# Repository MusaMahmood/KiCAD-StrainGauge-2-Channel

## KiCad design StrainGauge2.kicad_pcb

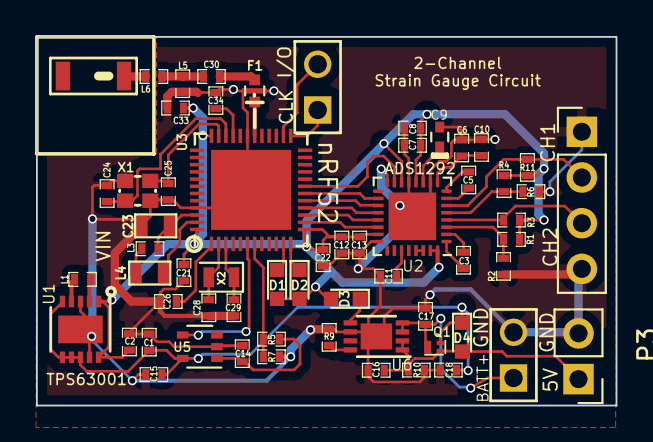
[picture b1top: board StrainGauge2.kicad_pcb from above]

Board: 2 copper layers, 32.2 x 20.5 mm, 61 parts (0 on the bottom side), 46 nets.

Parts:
A1: CHIP-ANT; JTI-2450AT18A100-CHIP-ANT
C1, C10, C14, C15: 10uF; SM0402
C2: 22uF; SM0402
C3, C5: 4.7 nF; SM0402
C6, C7, C12: 0.1uF; SM0402
C8, C11, C13: 1uF; SM0402
C9: 1uF; C_0402
C16, C17: 4.7uF; SM0402
C18: 1.0uF; SM0402
C21: 4.7µF; SM0402
C22, C26, C33: 100nF; SM0402
C23: 1.0µF; SM0603
C24, C25, C28, C29: 12pF; SM0402
C30: 1.0pF; SM0402
C34: 100pF; SM0402
D1, D2, D3: LED; LED_0603
D4: D_Schottky; LED_0603
F1: 2450FM07A0029; R_0402
L1: 2.20µH; SM0402
L3: 15nH; SM0402
L4: 10uH; SM0603
L5: 2.7nH; SM0402
L6: 3.9nH; SM0402
P1, P2: CONN_2; PIN_ARRAY_2X1
P3: CONN_2; Pin_Header_Straight_1x02_Pitch2.54mm
P5: CONN_01X04; Pin_Header_Straight_1x04_Pitch2.54mm
Q1: DMP21D5UFB4-7B; X2-DFN1006
R1, R2, R3, R4, R6, R11: 200k; SM0402
R5, R7: 1M; SM0402
R9: 2k; SM0402
R10: 100k; SM0402
U1: TPS63001; DFN-10-1EP_3x3mm_Pitch0.5mm
U2: ADS1291/2; QFN-32-1EP_4x4mm_Pitch0.4mm
U3: NRF528XX-QFAA; UQFN-48-1EP_6x6mm_Pitch0.4mm
U5: TPS2294x; SOT-353_SC-70-5
U6: MCP73831; DFN-8-1EP_3x2mm_Pitch0.5mm
X1: Crystal_GND24; CRYSTAL-SMD-2.0MMx1.6MM
X2: 32.768 kHz; Crystal_SMD_2012-2pin_2.0x1.2mm

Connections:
5V_in_charge: C16.1, D4.2, P3.1, Q1.1, R10.1, U6.1, U6.2
/AIN_BAT_DIV_VOLTAGE: R5.1, R7.2, U3.7
/BATT_IN: C17.1, P1.1, Q1.2, U6.3, U6.4
/DEC1: C26.1, U3.1
/DEC3: C34.1, U3.33
/DIN: U2.19, U3.17
/DOUT: U2.21, U3.15
/LED2: D1.1, U3.11
/LED3: D2.1, U3.12
/LOAD_SW_CTRL: U3.6, U5.4
/RF: C30.1, F1.4
/SG1_INPUT_1: P5.3, R3.2, U2.4
/SG2_INPUT_1: P5.2, R11.2, U2.6
/SPI_SCLK: U2.20, U3.16
/SPI_~CS: U2.18, U3.18
/SWDCLK: P2.1, U3.25
/SWDIO: P2.2, U3.26
/WB1_Vinverting: R1.2, R2.1, U2.3
/WB2_Vinverting: R4.2, R6.1, U2.5
/~DRDY: U2.22, U3.14
/~PWDN/RESET: U2.15, U3.19
DGND: C1.2, C2.2, C6.1, C7.1, C8.1, C9.2, C10.1, C11.2, C12.2, C13.2, C14.2, C15.2, C16.2, C17.2, C18.1, C21.1, C22.2, C23.2, C24.1, C25.1, C26.2, C28.2, C29.2, C33.1, C34.2, F1.1, F1.3, L5.2, P1.2, P3.2, P5.1, P5.4, R2.2, R6.2, R7.1, R9.2, R10.2, U1.3, U1.9, U1.11, U2.10, U2.13, U2.16, U2.24, U2.33, U3.31, U3.45, U3.49, U5.2, U6.6, U6.9, X1.2, X1.4
DVDD: C2.1, C7.2, C8.2, C12.1, C13.1, C21.2, C22.1, C33.2, D1.2, D2.2, D3.2, R1.1, R3.1, R4.1, R11.1, U1.1, U1.10, U2.12, U2.14, U2.23, U2.31, U2.32, U3.13, U3.36, U3.48
unnamed: A1.1, L6.2
unnamed: C3.1, U2.1
unnamed: C3.2, U2.2
unnamed: C5.1, U2.7
unnamed: C5.2, U2.8
unnamed: C9.1, U2.11
unnamed: C6.2, C10.2, U2.9
unnamed: C11.1, U2.27
unnamed: C14.1, R5.2, U5.1
unnamed: C23.1, L3.2, U3.46
unnamed: C24.2, U3.34, X1.1
unnamed: C25.2, U3.35, X1.3
unnamed: C28.1, U3.2, X2.2
unnamed: C29.1, U3.3, X2.1
unnamed: C30.2, L5.1, L6.1
unnamed: D3.1, U6.5
unnamed: F1.2, U3.30
unnamed: L1.1, U1.4
unnamed: L1.2, U1.2
unnamed: L3.1, L4.2
unnamed: L4.1, U3.47
unnamed: R9.1, U6.8
VCC: C1.1, C15.1, C18.2, D4.1, Q1.3, U1.5, U1.6, U1.7, U1.8, U5.5

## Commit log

2019-04-25 Initial Commit.
2019-04-26 Removed MPU from schematic and PCB.
2019-04-26 Remove Bias Circuit from schematic and pcb. Finalized circuits with wheatstone bridges.
2019-04-26 Schematic cleanup, final PCB Gerbers
